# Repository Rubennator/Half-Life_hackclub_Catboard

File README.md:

# Half-Life_hackclub_Catboard

A Midi keypad is pretty cool, but it can be made cooler!
In the first project (week 1) I made a Catbie, cat tamagotchi, only the face/head. So in this project I will be making the body of the cat. 

Image of the Catbie: 

So I can extend this face and make a real cat!

After some hours I have almost made the pcb:

Above you also see the head which is from the Catbie. This is how I could make sure it slotted in. Sadly it isn't possible to make the body more scaled to the head due to prices.
It wasn't easy to make my own footprint but eventually I actually made my very own pcb "component". For the shape of the it paw was worth the struggle.

Done the wiring and made the PCB look pretty cool with the silkscreen!

The firmware I took from the github of Kai and tried to make it fit my key-layout. The LED should also work. Only one way to find out in 5 weeks! :)
I learned quite a lot from the second time PCB-making. It isn't as hard as I thought. But it is expensive.... :(

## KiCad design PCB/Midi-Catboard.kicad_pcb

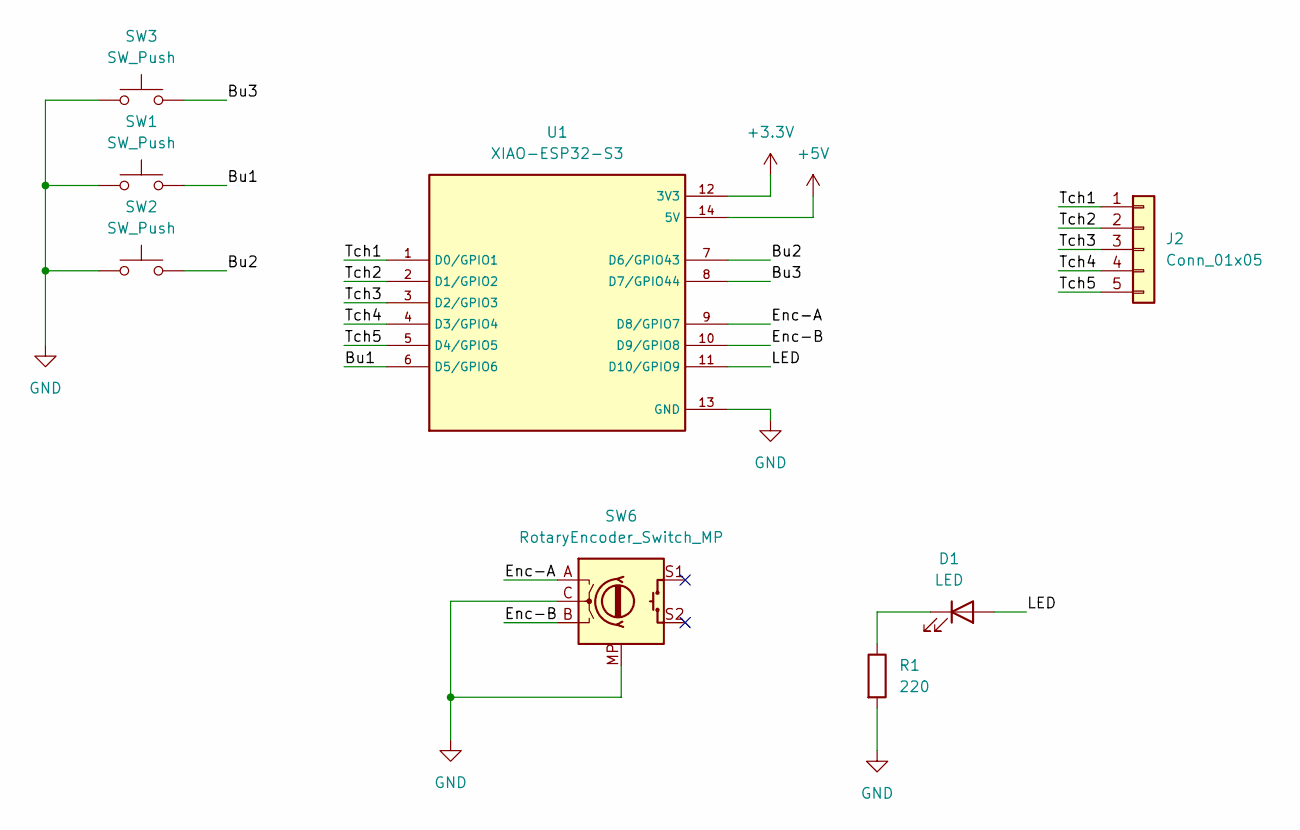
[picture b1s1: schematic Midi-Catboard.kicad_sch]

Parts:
D1: LED; LED_D5.0mm_Horizontal_O6.35mm_Z9.0mm
J2: Conn_01x05; Paw_Keys
R1: 220; R_Axial_DIN0204_L3.6mm_D1.6mm_P7.62mm_Horizontal
SW1, SW2, SW3: SW_Push; Kailh Choc Low-Profile Switches
SW6: RotaryEncoder_Switch_MP; RotaryEncoder_Alps_EC11E-Switch_Vertical_H20mm
U1: XIAO-ESP32-S3; XIAO ESP32-S3; PARTREV April 22nd, 2026

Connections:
+3.3V: U1.12 (3V3)
+5V: U1.14 (5V)
/Bu1: SW1.2, U1.6 (D5/GPIO6)
/Bu2: SW2.2, U1.7 (D6/GPIO43)
/Bu3: SW3.2, U1.8 (D7/GPIO44)
/Enc-A: SW6.A, U1.9 (D8/GPIO7)
/Enc-B: SW6.B, U1.10 (D9/GPIO8)
/LED: D1.2 (A), U1.11 (D10/GPIO9)
/Tch1: J2.1, U1.1 (D0/GPIO1)
/Tch2: J2.2, U1.2 (D1/GPIO2)
/Tch3: J2.3, U1.3 (D2/GPIO3)
/Tch4: J2.4, U1.4 (D3/GPIO4)
/Tch5: J2.5, U1.5 (D4/GPIO5)
GND: R1.2, SW1.1, SW2.1, SW3.1, SW6.C, SW6.MP, U1.13 (GND)
unnamed: D1.1 (K), R1.1

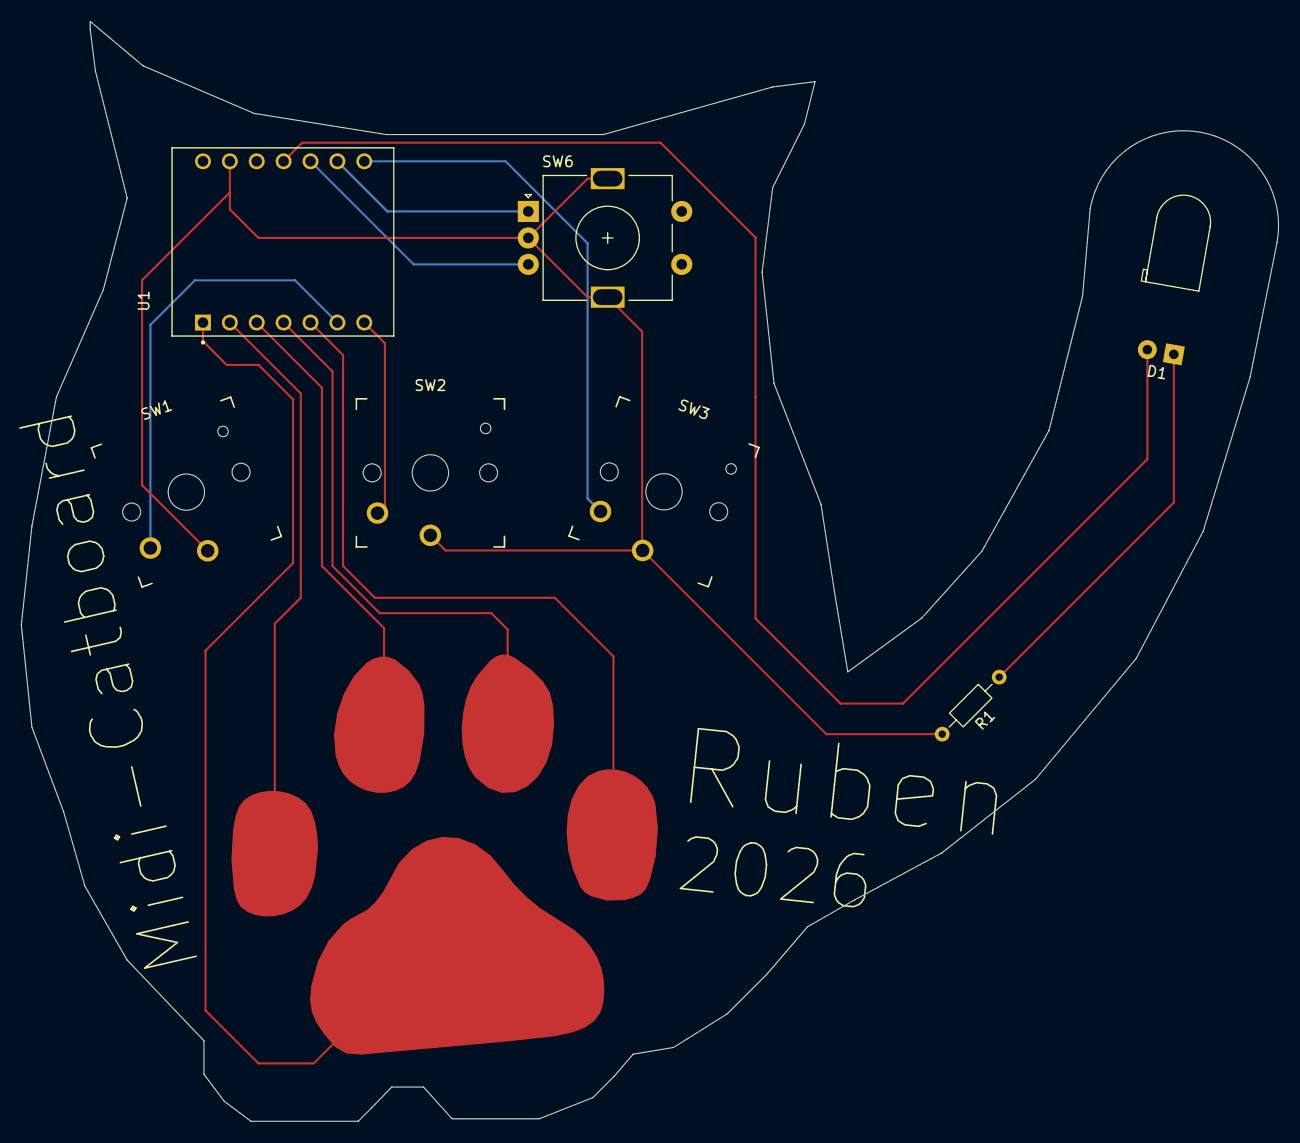
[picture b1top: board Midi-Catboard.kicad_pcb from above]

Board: 2 copper layers, 118.8 x 103.9 mm, 8 parts (0 on the bottom side), 13 nets.

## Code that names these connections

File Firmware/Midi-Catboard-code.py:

# From the KAI-tutorial github page
import keypad
import touchio
import digitalio #ADDED

from adafruit_midi.control_change import ControlChange
from microcontroller import pin

from kmk.extensions.media_keys import MediaKeys
#from kmk.extensions.rgb import RGB, AnimationModes
from kmk.keys import KC
from kmk.kmk_keyboard import KMKKeyboard
from kmk.modules.encoder import EncoderHandler
from kmk.modules.midi import MidiKeys
from kmk.modules.potentiometer import PotentiometerHandler
from kmk.scanners import Scanner
from kmk.scanners.keypad import KeysScanner

#From  circuitpython website to show where the pin is.
led = digitalio.DigitalInOut(pin.GPIO9)
led.direction = digitalio.Direction.OUTPUT

# KMK doesn't have a scanner for touch pads, so here's a tiny one.
# Don't touch the pads while the board boots - they calibrate on startup!
class TouchScanner(Scanner):
    def __init__(self, pins):
        self.pads = [touchio.TouchIn(p) for p in pins]
        self.pressed = [False] * len(pins)

    @property
    def key_count(self):
        return len(self.pads)

    def scan_for_changes(self):
        for i, pad in enumerate(self.pads):
            touched = pad.value #pad value true = touched
            if touched != self.pressed[i]:
                self.pressed[i] = touched
                led.value = touched #touched is when pad value is true
                return keypad.Event(i + self.offset, touched)


keyboard = KMKKeyboard()
# These have to be created before we use KC.MIDI_NOTE / KC.VOLU below
midi = MidiKeys()
media_keys = MediaKeys()

keyboard.matrix = [
    # Touch pads 1-5 (keys 0-4) EDITED
    TouchScanner([pin.GPIO5, pin.GPIO4, pin.GPIO3, pin.GPIO2, pin.GPIO1]),
    # Switches SW1-SW3 (keys 7-9)
    KeysScanner([pin.GPIO6, pin.GPIO43, pin.GPIO44], value_when_pressed=False, pull=True),
]

# Touch pads play a C major scale, switches play drum sounds
keyboard.keymap = [[
    KC.MIDI_NOTE(60), KC.MIDI_NOTE(62), KC.MIDI_NOTE(64),
    KC.MIDI_NOTE(67), KC.MIDI_NOTE(69),
    KC.MIDI_NOTE(36), KC.MIDI_NOTE(38), KC.MIDI_NOTE(42),  # kick, snare, hi-hat EDITED TO 8 NOTES NOT 10
]]

# Rotary encoder controls your computer's volume
encoder = EncoderHandler()
encoder.pins = ((pin.GPIO7, pin.GPIO8, None),)  # A = TX, B = RX, no button
encoder.map = [((KC.VOLD, KC.VOLU, KC.NO),)]

# Sliders send MIDI CC 1 (mod wheel) and CC 7 (volume)
#sliders = PotentiometerHandler()
#sliders.pins = (
#    (pin.GPIO2, lambda state: midi.send(ControlChange(1, state.position))),
#    (pin.GPIO1, lambda state: midi.send(ControlChange(7, state.position))),
#)

keyboard.modules = [midi, encoder]
keyboard.extensions = [
   media_keys,
#    RGB(pixel_pin=pin.GPIO9, num_pixels=3, val_default=80, animation_mode=AnimationModes.RAINBOW),
]

if __name__ == '__main__':
    keyboard.go()
